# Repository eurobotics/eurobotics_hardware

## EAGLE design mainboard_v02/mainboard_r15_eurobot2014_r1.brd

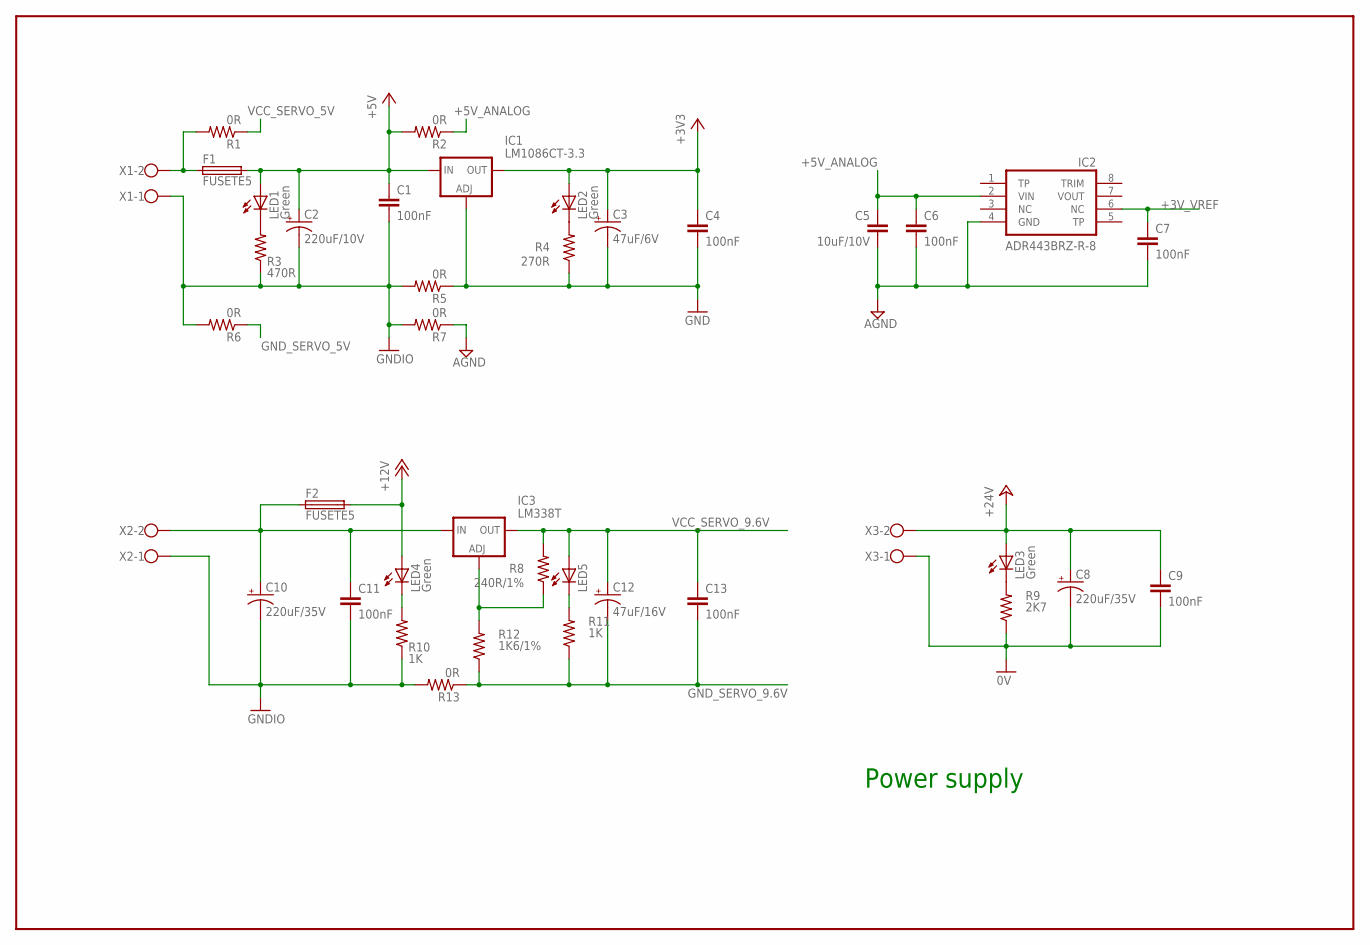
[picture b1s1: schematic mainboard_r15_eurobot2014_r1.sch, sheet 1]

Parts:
C1, C4, C6, C7, C9, C11, C13: 100nF; C0805
C2: 220uF/10V; E2,5-7
C3: 47uF/6V; SMC_D
C5: 10uF/10V; C1206
C8, C10: 220uF/35V; E5-10,5
C12: 47uF/16V; SMC_D
F1, F2: FUSETE5; TE5
IC1: LM1086CT-3.3; 317TS
IC2: ADR443BRZ-R-8; SOIC8
IC3: LM338T; 317TS
LED1, LED2, LED3, LED4: Green; CHIP-LED0805
LED5: LEDCHIP-LED0805; CHIP-LED0805
R1, R2, R5, R6, R7, R13: 0R; R0805
R3: 470R; R0805
R4: 270R; R0805
R8: 240R/1%; R0805
R9: 2K7; R0805
R10, R11: 1K; R0805
R12: 1K6/1%; R0805
X1, X2, X3: W237-02P; W237-132

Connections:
0V: C8.-, C9.2, R9.1, X3.1; also elsewhere on the board
+3V3: C3.+, C4.1, IC1.2 (OUT), LED2.A; also elsewhere on the board
+3V_VREF: C7.1, IC2.6 (NC); also elsewhere on the board
+5V: C1.1, C2.+, F1.2, IC1.3 (IN), LED1.A, R2.2; also elsewhere on the board
+5V_ANALOG: C5.1, C6.1, IC2.2 (VIN), R2.1; also elsewhere on the board
+12V: F2.2, LED4.A; also elsewhere on the board
+24V: C8.+, C9.1, LED3.A, X3.2; also elsewhere on the board
AGND: C5.2, C6.2, C7.2, IC2.4 (GND), R7.1; also elsewhere on the board
GND: C3.-, C4.2, IC1.1 (ADJ), R4.1, R5.1; also elsewhere on the board
GNDIO: C1.2, C2.-, C10.-, C11.2, R3.1, R5.2, R6.2, R7.2, R10.1, R13.2, X1.1, X2.1; also elsewhere on the board
GND_SERVO_5V: R6.1; also elsewhere on the board
GND_SERVO_9.6V: C12.-, C13.2, R11.1, R12.1, R13.1; also elsewhere on the board
unnamed: IC3.1 (ADJ), R8.1, R12.2
unnamed: LED5.C, R11.2
unnamed: C10.+, C11.1, F2.1, IC3.3 (IN), X2.2
unnamed: LED1.C, R3.2
unnamed: LED2.C, R4.2
unnamed: LED4.C, R10.2
unnamed: LED3.C, R9.2
unnamed: F1.1, R1.2, X1.2
VCC_SERVO_5V: R1.1; also elsewhere on the board
VCC_SERVO_9.6V: C12.+, C13.1, IC3.2 (OUT), LED5.A, R8.2; also elsewhere on the board

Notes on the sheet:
Power supply

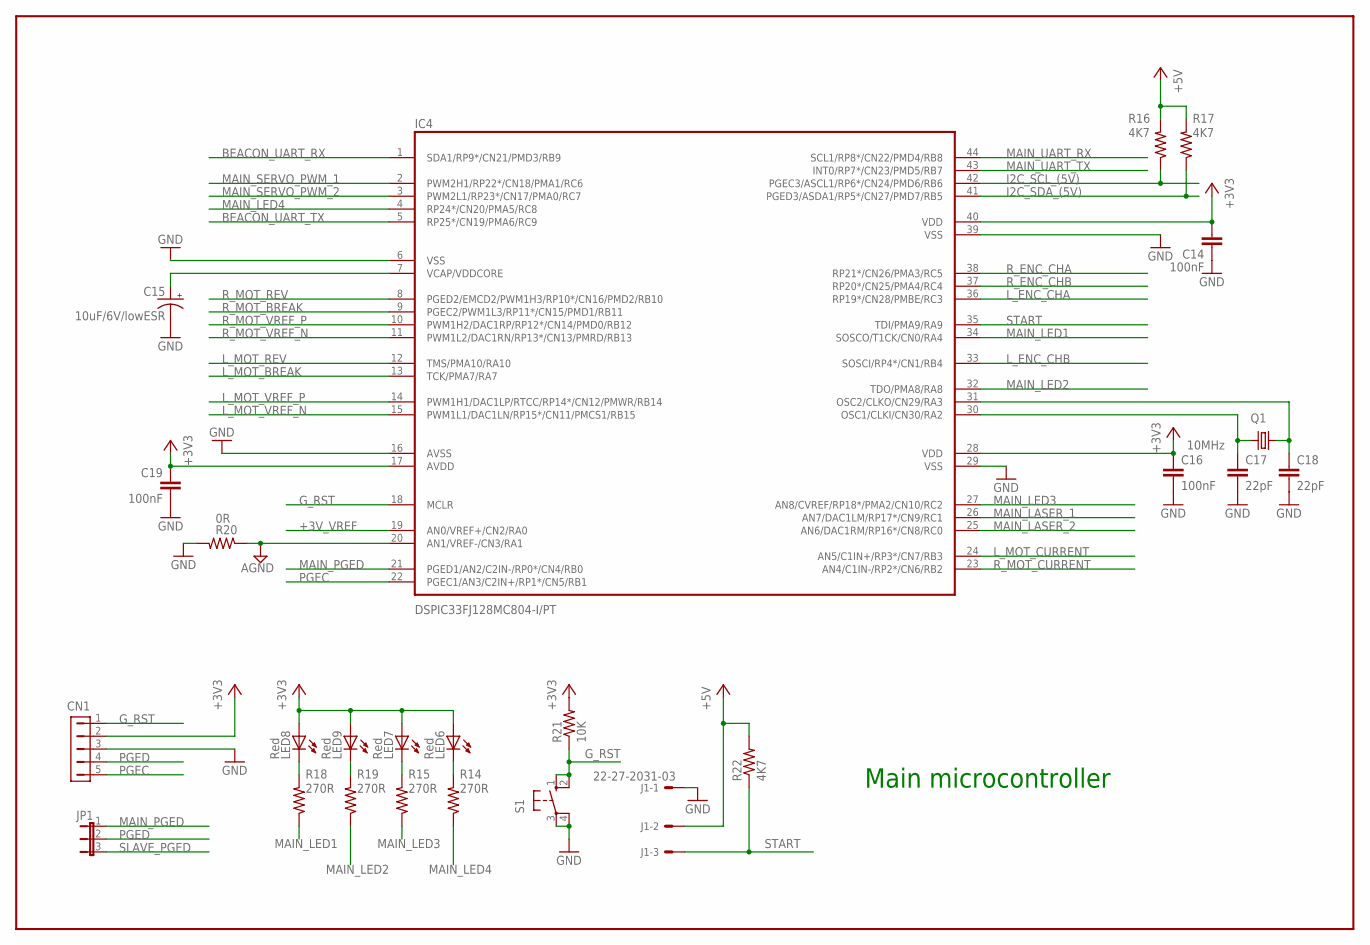
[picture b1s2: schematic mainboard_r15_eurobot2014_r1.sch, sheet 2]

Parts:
C14, C16, C19: 100nF; C0603
C15: 10uF/6V/lowESR; SMC_A
C17, C18: 22pF; C0805
CN1: HDR-1X5-SIP-100; SIP-100-5V
IC4: DSPIC33FJ128MC804-I/PT; TQFP44
J1: 22-27-2031-03; 6410-03
JP1: JP2E; JP2
LED6, LED7, LED8, LED9: Red; CHIP-LED0805
Q1: 10MHz; HC49UP
R14, R15, R18, R19: 270R; R0805
R16, R17, R22: 4K7; R0805
R20: 0R; R0805
R21: 10K; R0805
S1: 10-XX; B3F-10XX

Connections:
+3V3: C14.1, C16.1, C19.1, CN1.2, IC4.17 (AVDD), IC4.28 (VDD), IC4.40 (VDD), LED6.A, LED7.A, LED8.A, LED9.A, R21.2; also elsewhere on the board
+3V_VREF: IC4.19 (AN0/VREF+/CN2/RA0); also elsewhere on the board
+5V: J1.2, R16.2, R17.2, R22.2; also elsewhere on the board
AGND: IC4.20 (AN1/VREF-/CN3/RA1), R20.1; also elsewhere on the board
BEACON_UART_RX: IC4.1 (SDA1/RP9*/CN21/PMD3/RB9); also elsewhere on the board
BEACON_UART_TX: IC4.5 (RP25*/CN19/PMA6/RC9); also elsewhere on the board
GND: C14.2, C15.-, C16.2, C17.2, C18.2, C19.2, CN1.3, IC4.6 (VSS), IC4.16 (AVSS), IC4.29 (VSS), IC4.39 (VSS), J1.1, R20.2, S1.3, S1.4 (P1); also elsewhere on the board
G_RST: CN1.1, IC4.18 (MCLR), R21.1, S1.1 (S), S1.2 (S1); also elsewhere on the board
I2C_SCL_(5V): IC4.42 (PGEC3/ASCL1/RP6*/CN24/PMD6/RB6), R16.1; also elsewhere on the board
I2C_SDA_(5V): IC4.41 (PGED3/ASDA1/RP5*/CN27/PMD7/RB5), R17.1; also elsewhere on the board
L_ENC_CHA: IC4.36 (RP19*/CN28/PMBE/RC3); also elsewhere on the board
L_ENC_CHB: IC4.33 (SOSCI/RP4*/CN1/RB4); also elsewhere on the board
L_MOT_BREAK: IC4.13 (TCK/PMA7/RA7); also elsewhere on the board
L_MOT_CURRENT: IC4.24 (AN5/C1IN+/RP3*/CN7/RB3); also elsewhere on the board
L_MOT_REV: IC4.12 (TMS/PMA10/RA10); also elsewhere on the board
L_MOT_VREF_N: IC4.15 (PWM1L1/DAC1LN/RP15*/CN11/PMCS1/RB15); also elsewhere on the board
L_MOT_VREF_P: IC4.14 (PWM1H1/DAC1LP/RTCC/RP14*/CN12/PMWR/RB14); also elsewhere on the board
MAIN_LASER_1: IC4.26 (AN7/DAC1LM/RP17*/CN9/RC1); also elsewhere on the board
MAIN_LASER_2: IC4.25 (AN6/DAC1RM/RP16*/CN8/RC0); also elsewhere on the board
MAIN_LED1: IC4.34 (SOSCO/T1CK/CN0/RA4), R18.1
MAIN_LED2: IC4.32 (TDO/PMA8/RA8), R19.1
MAIN_LED3: IC4.27 (AN8/CVREF/RP18*/PMA2/CN10/RC2), R15.1
MAIN_LED4: IC4.4 (RP24*/CN20/PMA5/RC8), R14.1
MAIN_PGED: IC4.21 (PGED1/AN2/C2IN-/RP0*/CN4/RB0), JP1.1
MAIN_SERVO_PWM_1: IC4.2 (PWM2H1/RP22*/CN18/PMA1/RC6); also elsewhere on the board
MAIN_SERVO_PWM_2: IC4.3 (PWM2L1/RP23*/CN17/PMA0/RC7); also elsewhere on the board
MAIN_UART_RX: IC4.44 (SCL1/RP8*/CN22/PMD4/RB8); also elsewhere on the board
MAIN_UART_TX: IC4.43 (INT0/RP7*/CN23/PMD5/RB7); also elsewhere on the board
unnamed: LED8.C, R18.2
unnamed: LED9.C, R19.2
unnamed: LED7.C, R15.2
unnamed: LED6.C, R14.2
unnamed: C18.1, IC4.31 (OSC2/CLKO/CN29/RA3), Q1.2
unnamed: C17.1, IC4.30 (OSC1/CLKI/CN30/RA2), Q1.1
unnamed: C15.+, IC4.7 (VCAP/VDDCORE)
PGEC: CN1.5, IC4.22 (PGEC1/AN3/C2IN+/RP1*/CN5/RB1); also elsewhere on the board
PGED: CN1.4, JP1.2
R_ENC_CHA: IC4.38 (RP21*/CN26/PMA3/RC5); also elsewhere on the board
R_ENC_CHB: IC4.37 (RP20*/CN25/PMA4/RC4); also elsewhere on the board
R_MOT_BREAK: IC4.9 (PGEC2/PWM1L3/RP11*/CN15/PMD1/RB11); also elsewhere on the board
R_MOT_CURRENT: IC4.23 (AN4/C1IN-/RP2*/CN6/RB2); also elsewhere on the board
R_MOT_REV: IC4.8 (PGED2/EMCD2/PWM1H3/RP10*/CN16/PMD2/RB10); also elsewhere on the board
R_MOT_VREF_N: IC4.11 (PWM1L2/DAC1RN/RP13*/CN13/PMRD/RB13); also elsewhere on the board
R_MOT_VREF_P: IC4.10 (PWM1H2/DAC1RP/RP12*/CN14/PMD0/RB12); also elsewhere on the board
SLAVE_PGED: JP1.3; also elsewhere on the board
START: IC4.35 (TDI/PMA9/RA9), J1.3, R22.1

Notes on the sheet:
Main microcontroller

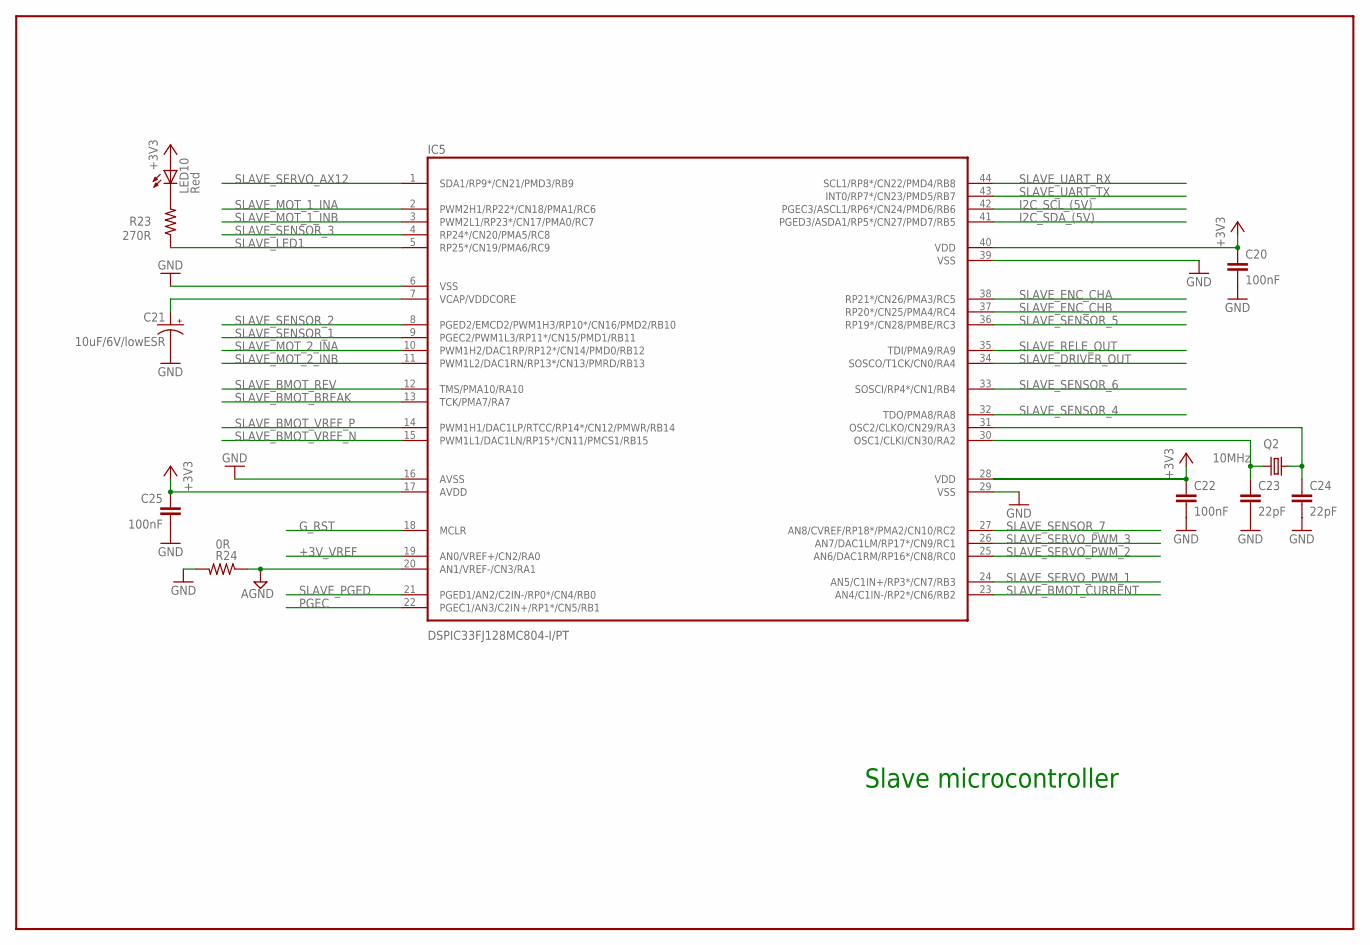
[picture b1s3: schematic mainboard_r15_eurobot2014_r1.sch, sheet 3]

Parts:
C20, C22, C25: 100nF; C0603
C21: 10uF/6V/lowESR; SMC_A
C23, C24: 22pF; C0805
IC5: DSPIC33FJ128MC804-I/PT; TQFP44
LED10: Red; CHIP-LED0805
Q2: 10MHz; HC49UP
R23: 270R; R0805
R24: 0R; R0805

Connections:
+3V3: C20.1, C22.1, C25.1, IC5.17 (AVDD), IC5.28 (VDD), IC5.40 (VDD), LED10.A; also elsewhere on the board
+3V_VREF: IC5.19 (AN0/VREF+/CN2/RA0); also elsewhere on the board
AGND: IC5.20 (AN1/VREF-/CN3/RA1), R24.1; also elsewhere on the board
GND: C20.2, C21.-, C22.2, C23.2, C24.2, C25.2, IC5.6 (VSS), IC5.16 (AVSS), IC5.29 (VSS), IC5.39 (VSS), R24.2; also elsewhere on the board
G_RST: IC5.18 (MCLR); also elsewhere on the board
I2C_SCL_(5V): IC5.42 (PGEC3/ASCL1/RP6*/CN24/PMD6/RB6); also elsewhere on the board
I2C_SDA_(5V): IC5.41 (PGED3/ASDA1/RP5*/CN27/PMD7/RB5); also elsewhere on the board
unnamed: LED10.C, R23.2
unnamed: C24.1, IC5.31 (OSC2/CLKO/CN29/RA3), Q2.2
unnamed: C23.1, IC5.30 (OSC1/CLKI/CN30/RA2), Q2.1
unnamed: C21.+, IC5.7 (VCAP/VDDCORE)
PGEC: IC5.22 (PGEC1/AN3/C2IN+/RP1*/CN5/RB1); also elsewhere on the board
SLAVE_BMOT_BREAK: IC5.13 (TCK/PMA7/RA7); also elsewhere on the board
SLAVE_BMOT_CURRENT: IC5.23 (AN4/C1IN-/RP2*/CN6/RB2); also elsewhere on the board
SLAVE_BMOT_REV: IC5.12 (TMS/PMA10/RA10); also elsewhere on the board
SLAVE_BMOT_VREF_N: IC5.15 (PWM1L1/DAC1LN/RP15*/CN11/PMCS1/RB15); also elsewhere on the board
SLAVE_BMOT_VREF_P: IC5.14 (PWM1H1/DAC1LP/RTCC/RP14*/CN12/PMWR/RB14); also elsewhere on the board
SLAVE_DRIVER_OUT: IC5.34 (SOSCO/T1CK/CN0/RA4); also elsewhere on the board
SLAVE_ENC_CHA: IC5.38 (RP21*/CN26/PMA3/RC5); also elsewhere on the board
SLAVE_ENC_CHB: IC5.37 (RP20*/CN25/PMA4/RC4); also elsewhere on the board
SLAVE_LED1: IC5.5 (RP25*/CN19/PMA6/RC9), R23.1
SLAVE_MOT_1_INA: IC5.2 (PWM2H1/RP22*/CN18/PMA1/RC6); also elsewhere on the board
SLAVE_MOT_1_INB: IC5.3 (PWM2L1/RP23*/CN17/PMA0/RC7); also elsewhere on the board
SLAVE_MOT_2_INA: IC5.10 (PWM1H2/DAC1RP/RP12*/CN14/PMD0/RB12); also elsewhere on the board
SLAVE_MOT_2_INB: IC5.11 (PWM1L2/DAC1RN/RP13*/CN13/PMRD/RB13); also elsewhere on the board
SLAVE_PGED: IC5.21 (PGED1/AN2/C2IN-/RP0*/CN4/RB0); also elsewhere on the board
SLAVE_RELE_OUT: IC5.35 (TDI/PMA9/RA9); also elsewhere on the board
SLAVE_SENSOR_1: IC5.9 (PGEC2/PWM1L3/RP11*/CN15/PMD1/RB11); also elsewhere on the board
SLAVE_SENSOR_2: IC5.8 (PGED2/EMCD2/PWM1H3/RP10*/CN16/PMD2/RB10); also elsewhere on the board
SLAVE_SENSOR_3: IC5.4 (RP24*/CN20/PMA5/RC8); also elsewhere on the board
SLAVE_SENSOR_4: IC5.32 (TDO/PMA8/RA8); also elsewhere on the board
SLAVE_SENSOR_5: IC5.36 (RP19*/CN28/PMBE/RC3); also elsewhere on the board
SLAVE_SENSOR_6: IC5.33 (SOSCI/RP4*/CN1/RB4); also elsewhere on the board
SLAVE_SENSOR_7: IC5.27 (AN8/CVREF/RP18*/PMA2/CN10/RC2); also elsewhere on the board
SLAVE_SERVO_AX12: IC5.1 (SDA1/RP9*/CN21/PMD3/RB9); also elsewhere on the board
SLAVE_SERVO_PWM_1: IC5.24 (AN5/C1IN+/RP3*/CN7/RB3); also elsewhere on the board
SLAVE_SERVO_PWM_2: IC5.25 (AN6/DAC1RM/RP16*/CN8/RC0); also elsewhere on the board
SLAVE_SERVO_PWM_3: IC5.26 (AN7/DAC1LM/RP17*/CN9/RC1); also elsewhere on the board
SLAVE_UART_RX: IC5.44 (SCL1/RP8*/CN22/PMD4/RB8); also elsewhere on the board
SLAVE_UART_TX: IC5.43 (INT0/RP7*/CN23/PMD5/RB7); also elsewhere on the board

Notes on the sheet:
Slave microcontroller

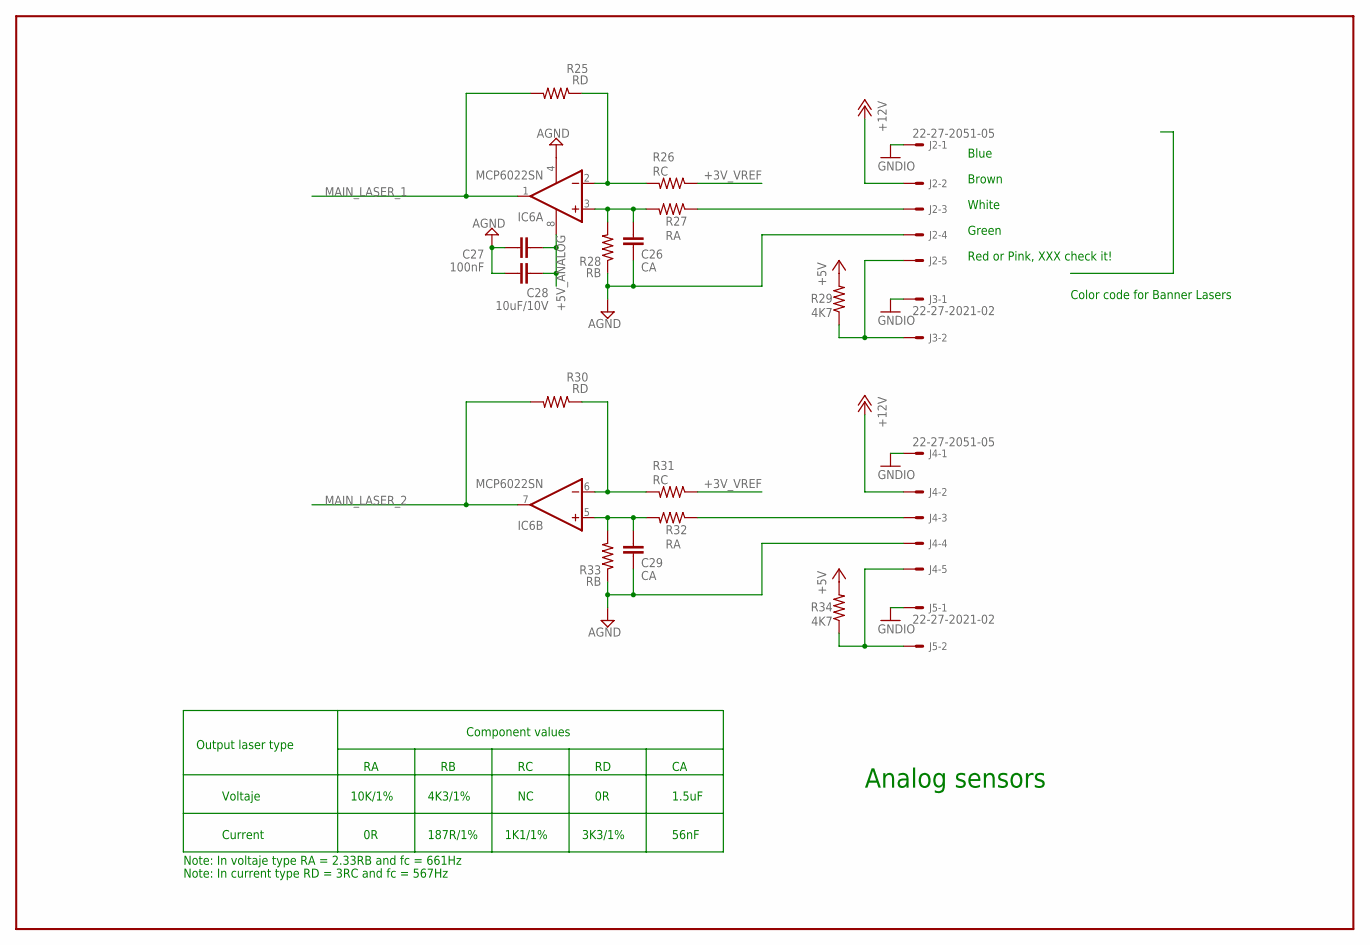
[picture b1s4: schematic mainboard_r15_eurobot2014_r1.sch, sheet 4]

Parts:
C26, C29: CA; C0805
C27: 100nF; C0805
C28: 10uF/10V; C1206
IC6: MCP6022SN; SO08
J2, J4: 22-27-2051-05; 6410-05
J3, J5: 22-27-2021-02; 6410-02
R25, R30: RD; R0805
R26, R31: RC; R0805
R27, R32: RA; R0805
R28, R33: RB; R0805
R29, R34: 4K7; R0805

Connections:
+3V_VREF: R26.1, R31.1; also elsewhere on the board
+5V: R29.2, R34.2; also elsewhere on the board
+5V_ANALOG: C27.1, C28.2, IC6.8 (V+); also elsewhere on the board
+12V: J2.2, J4.2; also elsewhere on the board
AGND: C26.2, C27.2, C28.1, C29.2, IC6.4 (V-), J2.4, J4.4, R28.1, R33.1; also elsewhere on the board
GNDIO: J2.1, J3.1, J4.1, J5.1; also elsewhere on the board
MAIN_LASER_1: IC6.1 (OUT), R25.2; also elsewhere on the board
MAIN_LASER_2: IC6.7 (OUT), R30.2; also elsewhere on the board
unnamed: J2.3, R27.1
unnamed: J4.5, J5.2, R34.1
unnamed: J2.5, J3.2, R29.1
unnamed: IC6.2 (-IN), R25.1, R26.2
unnamed: C26.1, IC6.3 (+IN), R27.2, R28.2
unnamed: IC6.6 (-IN), R30.1, R31.2
unnamed: C29.1, IC6.5 (+IN), R32.2, R33.2
unnamed: J4.3, R32.1

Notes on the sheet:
Analog sensors
Component values
Output laser type
Voltaje
Current
4K3/1%
10K/1%
187R/1%
1K1/1%
3K3/1%
Note: In voltaje type RA = 2.33RB and fc = 661Hz
Note: In current type RD = 3RC and fc = 567Hz
1.5uF
56nF
Blue
Brown
White
Green
Red or Pink, XXX check it!
Color code for Banner Lasers

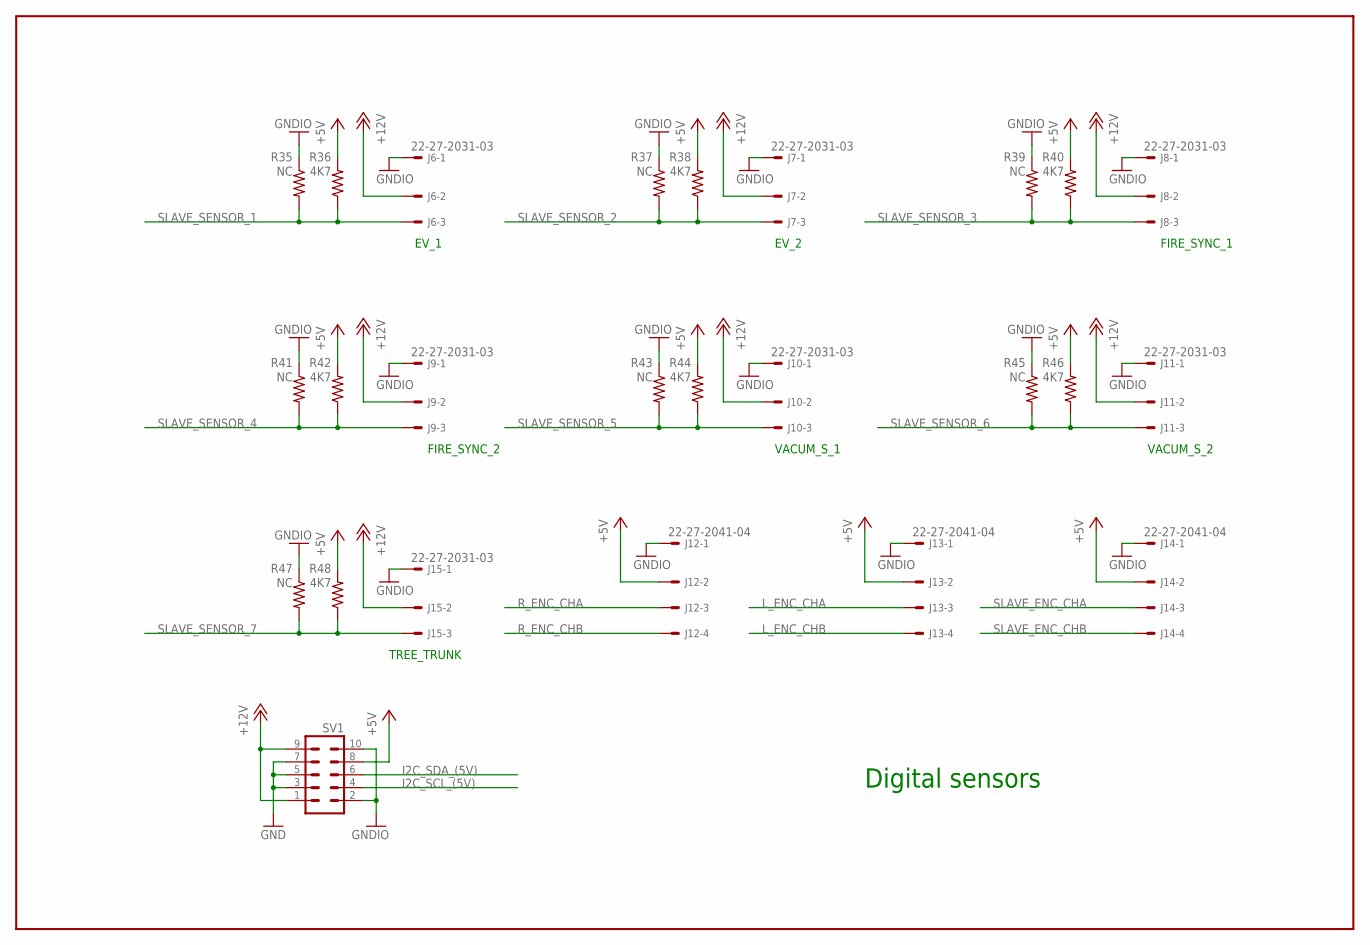
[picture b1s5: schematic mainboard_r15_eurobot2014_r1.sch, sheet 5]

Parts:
J6, J7, J8, J9, J10, J11, J15: 22-27-2031-03; 6410-03
J12, J13, J14: 22-27-2041-04; 6410-04
R35, R37, R39, R41, R43, R45, R47: NC; R0805
R36, R38, R40, R42, R44, R46, R48: 4K7; R0805
SV1: ML10

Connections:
+5V: J12.2, J13.2, J14.2, R36.2, R38.2, R40.2, R42.2, R44.2, R46.2, R48.2, SV1.8; also elsewhere on the board
+12V: J6.2, J7.2, J8.2, J9.2, J10.2, J11.2, J15.2, SV1.1, SV1.9; also elsewhere on the board
GND: SV1.3, SV1.5, SV1.7; also elsewhere on the board
GNDIO: J6.1, J7.1, J8.1, J9.1, J10.1, J11.1, J12.1, J13.1, J14.1, J15.1, R35.1, R37.1, R39.1, R41.1, R43.1, R45.1, R47.1, SV1.2, SV1.10; also elsewhere on the board
I2C_SCL_(5V): SV1.4; also elsewhere on the board
I2C_SDA_(5V): SV1.6; also elsewhere on the board
L_ENC_CHA: J13.3; also elsewhere on the board
L_ENC_CHB: J13.4; also elsewhere on the board
R_ENC_CHA: J12.3; also elsewhere on the board
R_ENC_CHB: J12.4; also elsewhere on the board
SLAVE_ENC_CHA: J14.3; also elsewhere on the board
SLAVE_ENC_CHB: J14.4; also elsewhere on the board
SLAVE_SENSOR_1: J6.3, R35.2, R36.1; also elsewhere on the board
SLAVE_SENSOR_2: J7.3, R37.2, R38.1; also elsewhere on the board
SLAVE_SENSOR_3: J8.3, R39.2, R40.1; also elsewhere on the board
SLAVE_SENSOR_4: J9.3, R41.2, R42.1; also elsewhere on the board
SLAVE_SENSOR_5: J10.3, R43.2, R44.1; also elsewhere on the board
SLAVE_SENSOR_6: J11.3, R45.2, R46.1; also elsewhere on the board
SLAVE_SENSOR_7: J15.3, R47.2, R48.1; also elsewhere on the board

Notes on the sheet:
Digital sensors
FIRE_SYNC_1
FIRE_SYNC_2
VACUM_S_1
VACUM_S_2
TREE_TRUNK
EV_1
EV_2

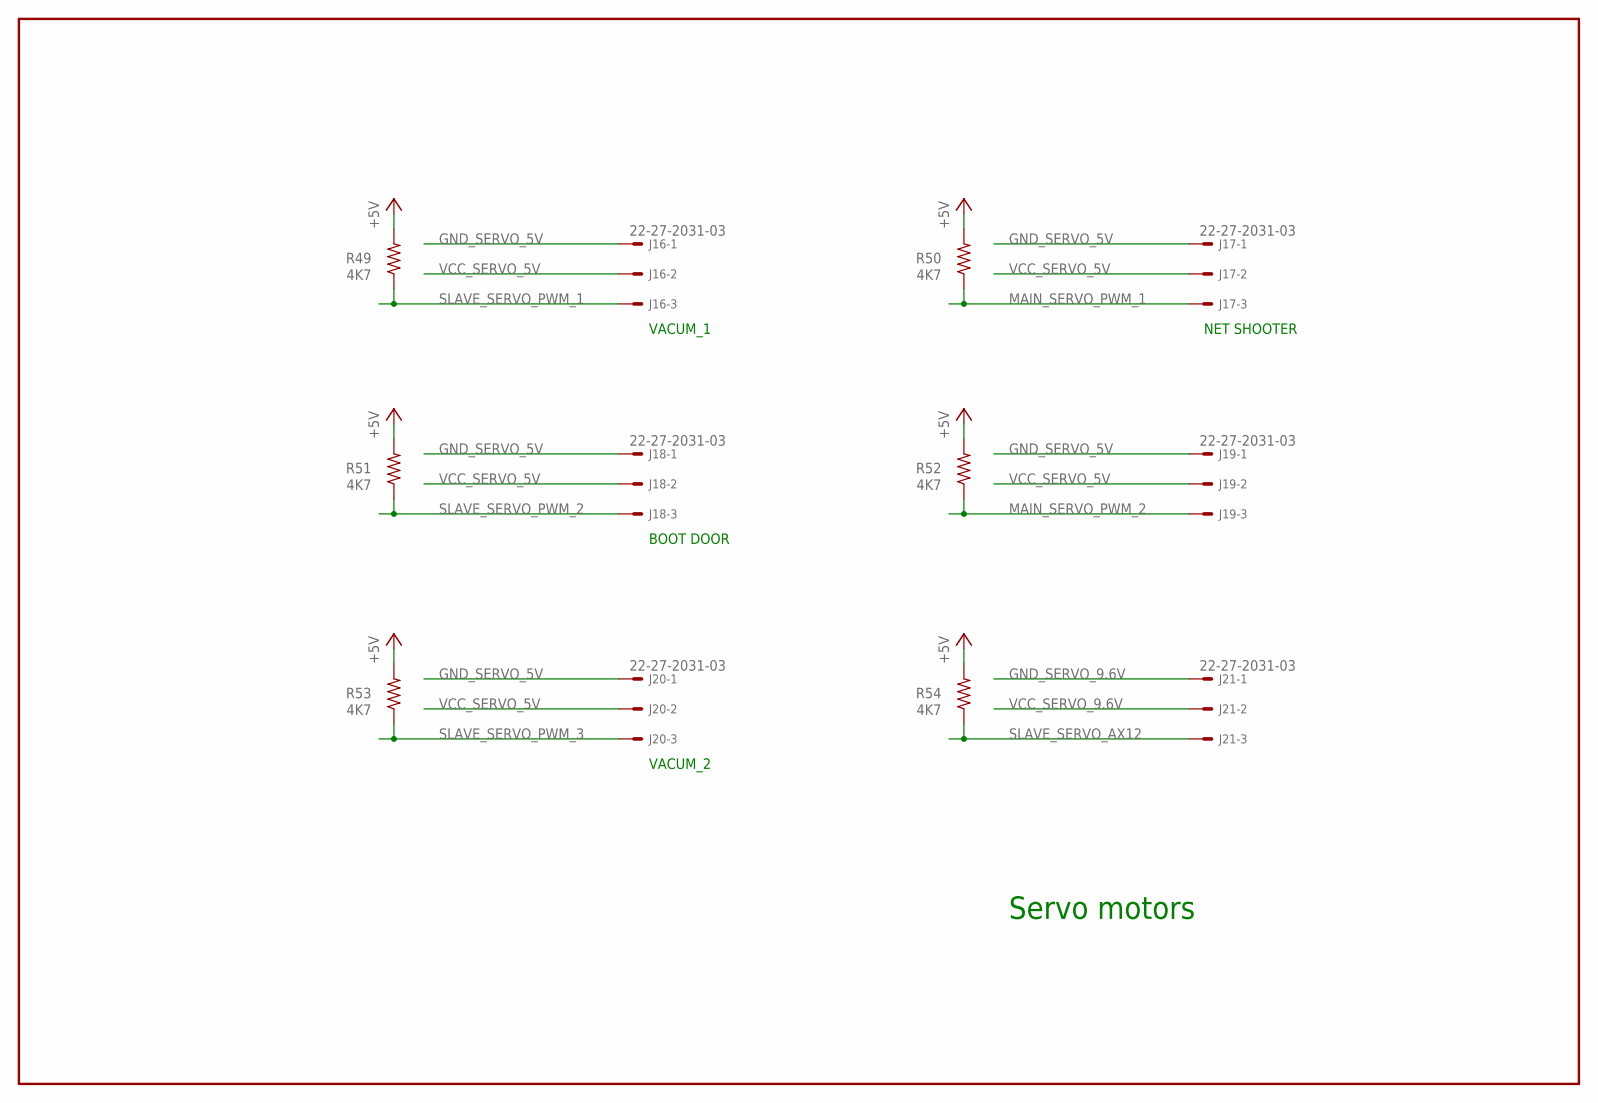
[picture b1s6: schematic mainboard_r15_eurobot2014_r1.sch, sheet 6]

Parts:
J16, J17, J18, J19, J20, J21: 22-27-2031-03; 6410-03
R49, R50, R51, R52, R53, R54: 4K7; R0805

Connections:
+5V: R49.2, R50.2, R51.2, R52.2, R53.2, R54.2; also elsewhere on the board
GND_SERVO_5V: J16.1, J17.1, J18.1, J19.1, J20.1; also elsewhere on the board
GND_SERVO_9.6V: J21.1; also elsewhere on the board
MAIN_SERVO_PWM_1: J17.3, R50.1; also elsewhere on the board
MAIN_SERVO_PWM_2: J19.3, R52.1; also elsewhere on the board
SLAVE_SERVO_AX12: J21.3, R54.1; also elsewhere on the board
SLAVE_SERVO_PWM_1: J16.3, R49.1; also elsewhere on the board
SLAVE_SERVO_PWM_2: J18.3, R51.1; also elsewhere on the board
SLAVE_SERVO_PWM_3: J20.3, R53.1; also elsewhere on the board
VCC_SERVO_5V: J16.2, J17.2, J18.2, J19.2, J20.2; also elsewhere on the board
VCC_SERVO_9.6V: J21.2; also elsewhere on the board

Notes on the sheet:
Servo motors
BOOT DOOR
VACUM_1
VACUM_2
NET SHOOTER

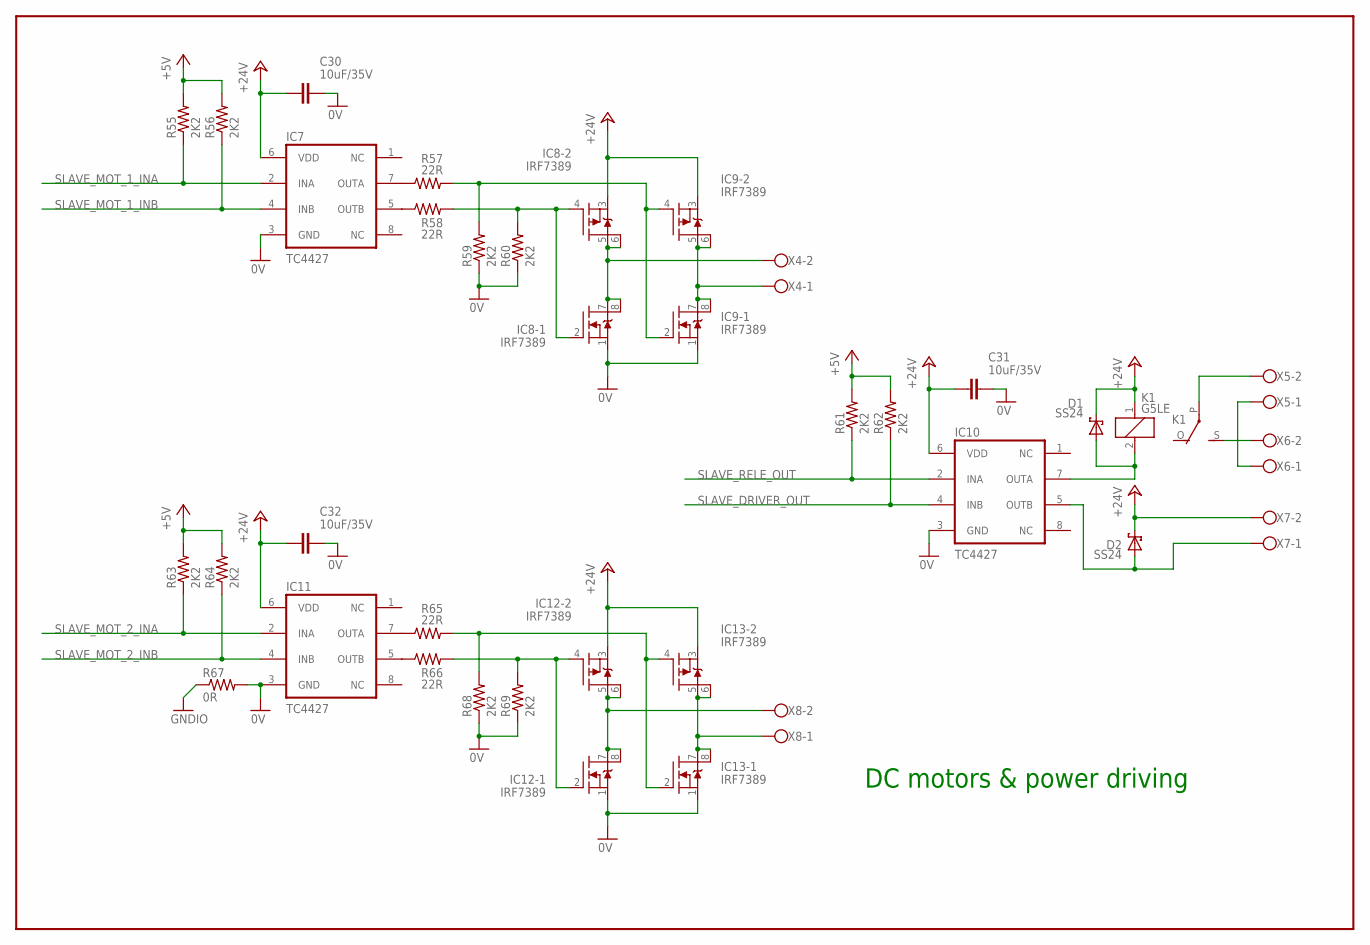
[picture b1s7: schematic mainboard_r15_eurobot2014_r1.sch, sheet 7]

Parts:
C30, C31, C32: 10uF/35V; C1206
D1, D2: SS24; DIOM5436X265N
IC7, IC10, IC11: TC4427; SO08
IC8, IC9, IC12, IC13: IRF7389; SO08
K1: G5LE
R55, R56, R59, R60, R61, R62, R63, R64, R68, R69: 2K2; R0805
R57, R58, R65, R66: 22R; R0805
R67: 0R; R0805
X4, X5, X6, X7, X8: W237-02P; W237-132

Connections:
0V: C30.1, C31.1, C32.1, IC7.3 (GND), IC8.1 (S), IC9.1 (S), IC10.3 (GND), IC11.3 (GND), IC12.1 (S), IC13.1 (S), R59.1, R60.1, R67.2, R68.1, R69.1; also elsewhere on the board
+5V: R55.2, R56.2, R61.2, R62.2, R63.2, R64.2; also elsewhere on the board
+24V: C30.2, C31.2, C32.2, D1.K, D2.K, IC7.6 (VDD), IC8.3 (S), IC9.3 (S), IC10.6 (VDD), IC11.6 (VDD), IC12.3 (S), IC13.3 (S), K1.1, X7.2; also elsewhere on the board
GNDIO: R67.1; also elsewhere on the board
unnamed: IC8.5 (D), IC8.6 (D), IC8.7 (D), IC8.8 (D), X4.2
unnamed: IC9.5 (D), IC9.6 (D), IC9.7 (D), IC9.8 (D), X4.1
unnamed: IC8.2 (G), IC8.4 (G), R58.2, R60.2
unnamed: IC9.2 (G), IC9.4 (G), R57.2, R59.2
unnamed: IC7.7 (OUTA), R57.1
unnamed: IC7.5 (OUTB), R58.1
unnamed: IC12.5 (D), IC12.6 (D), IC12.7 (D), IC12.8 (D), X8.2
unnamed: IC13.5 (D), IC13.6 (D), IC13.7 (D), IC13.8 (D), X8.1
unnamed: IC12.2 (G), IC12.4 (G), R66.2, R69.2
unnamed: IC13.2 (G), IC13.4 (G), R65.2, R68.2
unnamed: IC11.7 (OUTA), R65.1
unnamed: IC11.5 (OUTB), R66.1
unnamed: D1.A, IC10.7 (OUTA), K1.2
unnamed: X5.1, X6.1
unnamed: K1.P, X5.2
unnamed: K1.S, X6.2
unnamed: D2.A, IC10.5 (OUTB), X7.1
SLAVE_DRIVER_OUT: IC10.4 (INB), R62.1; also elsewhere on the board
SLAVE_MOT_1_INA: IC7.2 (INA), R55.1; also elsewhere on the board
SLAVE_MOT_1_INB: IC7.4 (INB), R56.1; also elsewhere on the board
SLAVE_MOT_2_INA: IC11.2 (INA), R63.1; also elsewhere on the board
SLAVE_MOT_2_INB: IC11.4 (INB), R64.1; also elsewhere on the board
SLAVE_RELE_OUT: IC10.2 (INA), R61.1; also elsewhere on the board

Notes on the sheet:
DC motors & power driving

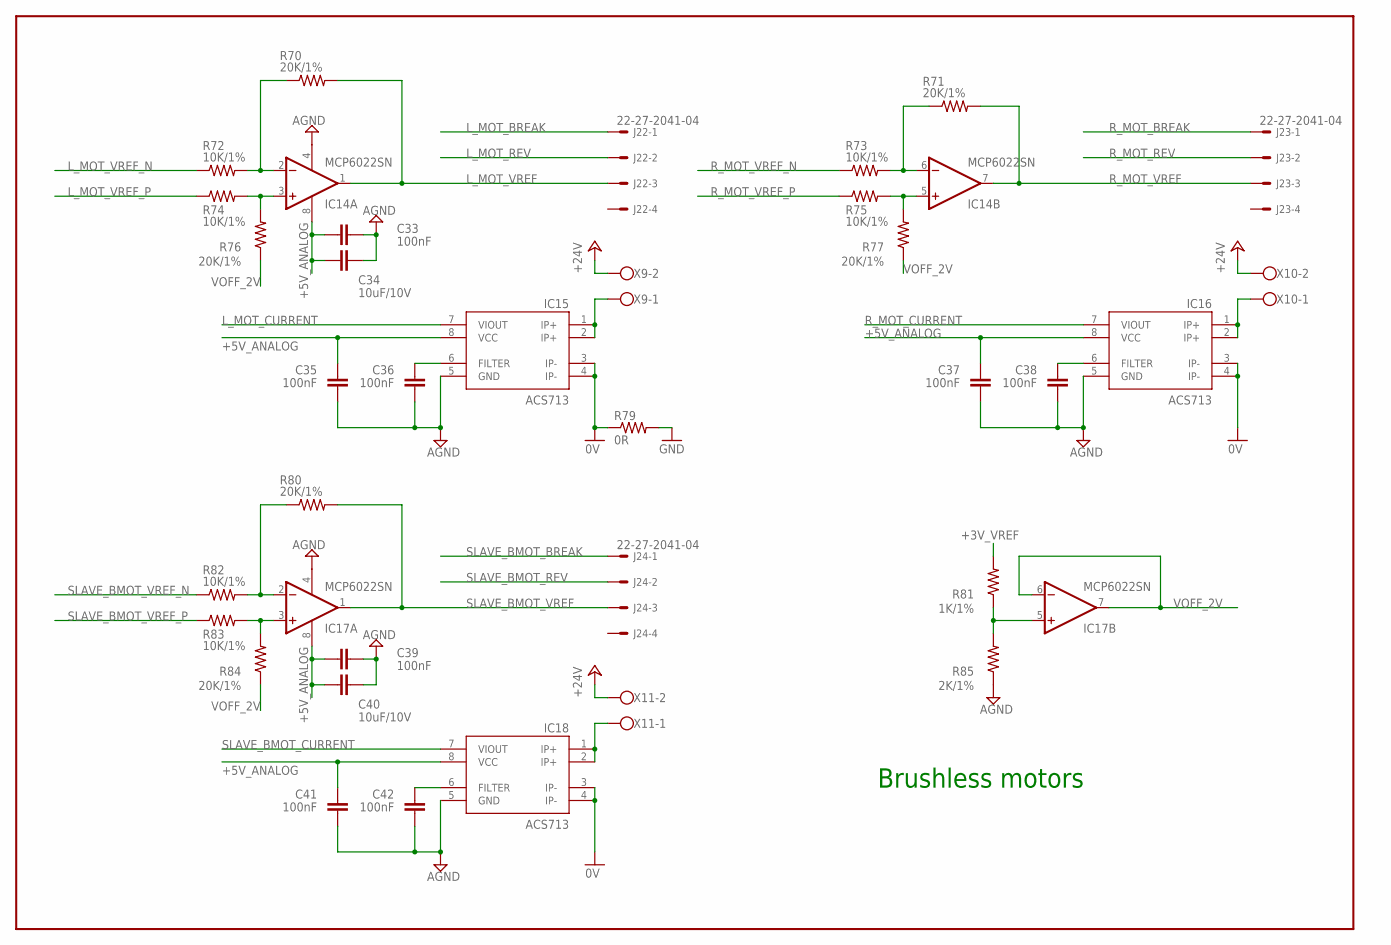
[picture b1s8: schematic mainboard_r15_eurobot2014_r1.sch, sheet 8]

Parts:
C33, C35, C36, C37, C38, C39, C41, C42: 100nF; C0805
C34, C40: 10uF/10V; C1206
IC14, IC17: MCP6022SN; SO08
IC15, IC16, IC18: ACS713; SO08
J22, J23, J24: 22-27-2041-04; 6410-04
R70, R71, R76, R77, R80, R84: 20K/1%; R0805
R72, R73, R74, R75, R82, R83: 10K/1%; R0805
R79: 0R; R0805
R81: 1K/1%; R0805
R85: 2K/1%; R0805
X9, X10, X11: W237-02P; W237-132

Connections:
0V: IC15.3 (IP-), IC15.4 (IP-), IC16.3 (IP-), IC16.4 (IP-), IC18.3 (IP-), IC18.4 (IP-), R79.1; also elsewhere on the board
+3V_VREF: R81.2; also elsewhere on the board
+5V_ANALOG: C33.1, C34.2, C35.2, C37.2, C39.1, C40.2, C41.2, IC14.8 (V+), IC15.8 (VCC), IC16.8 (VCC), IC17.8 (V+), IC18.8 (VCC); also elsewhere on the board
+24V: X9.2, X10.2, X11.2; also elsewhere on the board
AGND: C33.2, C34.1, C35.1, C36.1, C37.1, C38.1, C39.2, C40.1, C41.1, C42.1, IC14.4 (V-), IC15.5 (GND), IC16.5 (GND), IC17.4 (V-), IC18.5 (GND), R85.1; also elsewhere on the board
GND: R79.2; also elsewhere on the board
L_MOT_BREAK: J22.1; also elsewhere on the board
L_MOT_CURRENT: IC15.7 (VIOUT); also elsewhere on the board
L_MOT_REV: J22.2; also elsewhere on the board
L_MOT_VREF: IC14.1 (OUT), J22.3, R70.2
L_MOT_VREF_N: R72.1; also elsewhere on the board
L_MOT_VREF_P: R74.1; also elsewhere on the board
unnamed: IC14.2 (-IN), R70.1, R72.2
unnamed: IC14.3 (+IN), R74.2, R76.2
unnamed: IC14.6 (-IN), R71.1, R73.2
unnamed: IC15.1 (IP+), IC15.2 (IP+), X9.1
unnamed: C36.2, IC15.6 (FILTER)
unnamed: IC14.5 (+IN), R75.2, R77.2
unnamed: IC17.5 (+IN), R81.1, R85.2
unnamed: IC16.1 (IP+), IC16.2 (IP+), X10.1
unnamed: C38.2, IC16.6 (FILTER)
unnamed: IC18.1 (IP+), IC18.2 (IP+), X11.1
unnamed: C42.2, IC18.6 (FILTER)
unnamed: IC17.2 (-IN), R80.1, R82.2
unnamed: IC17.3 (+IN), R83.2, R84.2
R_MOT_BREAK: J23.1; also elsewhere on the board
R_MOT_CURRENT: IC16.7 (VIOUT); also elsewhere on the board
R_MOT_REV: J23.2; also elsewhere on the board
R_MOT_VREF: IC14.7 (OUT), J23.3, R71.2
R_MOT_VREF_N: R73.1; also elsewhere on the board
R_MOT_VREF_P: R75.1; also elsewhere on the board
SLAVE_BMOT_BREAK: J24.1; also elsewhere on the board
SLAVE_BMOT_CURRENT: IC18.7 (VIOUT); also elsewhere on the board
SLAVE_BMOT_REV: J24.2; also elsewhere on the board
SLAVE_BMOT_VREF: IC17.1 (OUT), J24.3, R80.2
SLAVE_BMOT_VREF_N: R82.1; also elsewhere on the board
SLAVE_BMOT_VREF_P: R83.1; also elsewhere on the board
VOFF_2V: IC17.6 (-IN), IC17.7 (OUT), R76.1, R77.1, R84.1

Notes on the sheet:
Brushless motors

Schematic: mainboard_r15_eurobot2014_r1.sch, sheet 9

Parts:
C43, C44, C45, C46, C47: 100nF; C0603
CON1: DB9F/90; D-09F/90
IC19, IC20: WT11A; WT11
IC21: MAX232ACSE; SO16
JP2, JP3: JP3Q

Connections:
+3V3: C44.2, C45.2, IC19.2 (VDD), IC19.16 (VDD), IC20.2 (VDD), IC20.16 (VDD), IC21.16 (VCC); also elsewhere on the board
BEACON_UART_RX: IC20.26 (TXD); also elsewhere on the board
BEACON_UART_TX: IC20.6 (RXD); also elsewhere on the board
FROM_TX_RS232_M: CON1.3, IC21.13 (R1IN)
GND: C45.1, C47.1, CON1.5, IC19.1 (GND), IC19.14 (GND), IC19.15 (GND), IC19.17 (RES), IC19.28 (GND), IC20.1 (GND), IC20.14 (GND), IC20.15 (GND), IC20.17 (RES), IC20.28 (GND), IC21.8 (R2IN), IC21.10 (T2IN), IC21.15 (GND); also elsewhere on the board
MAIN_UART_RX: JP2.1, JP3.2; also elsewhere on the board
MAIN_UART_TX: JP2.2, JP3.1; also elsewhere on the board
unnamed: IC20.5 (NRTS), IC20.10 (NCTS)
unnamed: C43.2, IC21.1 (C1+)
unnamed: C43.1, IC21.3 (C1-)
unnamed: C46.2, IC21.4 (C2+)
unnamed: C46.1, IC21.5 (C2-)
unnamed: C44.1, IC21.2 (V+)
unnamed: C47.2, IC21.6 (V-)
unnamed: IC19.5 (NRTS), IC19.10 (NCTS)
RX_MAX232: IC21.12 (R1OUT), JP3.4
RX_WT11: IC19.6 (RXD), JP2.4
SLAVE_UART_RX: JP2.5, JP3.6; also elsewhere on the board
SLAVE_UART_TX: JP2.6, JP3.5; also elsewhere on the board
TO_RX_RS232_M: CON1.2, IC21.14 (T1OUT)
TX_MAX232: IC21.11 (T1IN), JP3.3
TX_WT11: IC19.26 (TXD), JP2.3

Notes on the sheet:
Bluetooth and RS232
